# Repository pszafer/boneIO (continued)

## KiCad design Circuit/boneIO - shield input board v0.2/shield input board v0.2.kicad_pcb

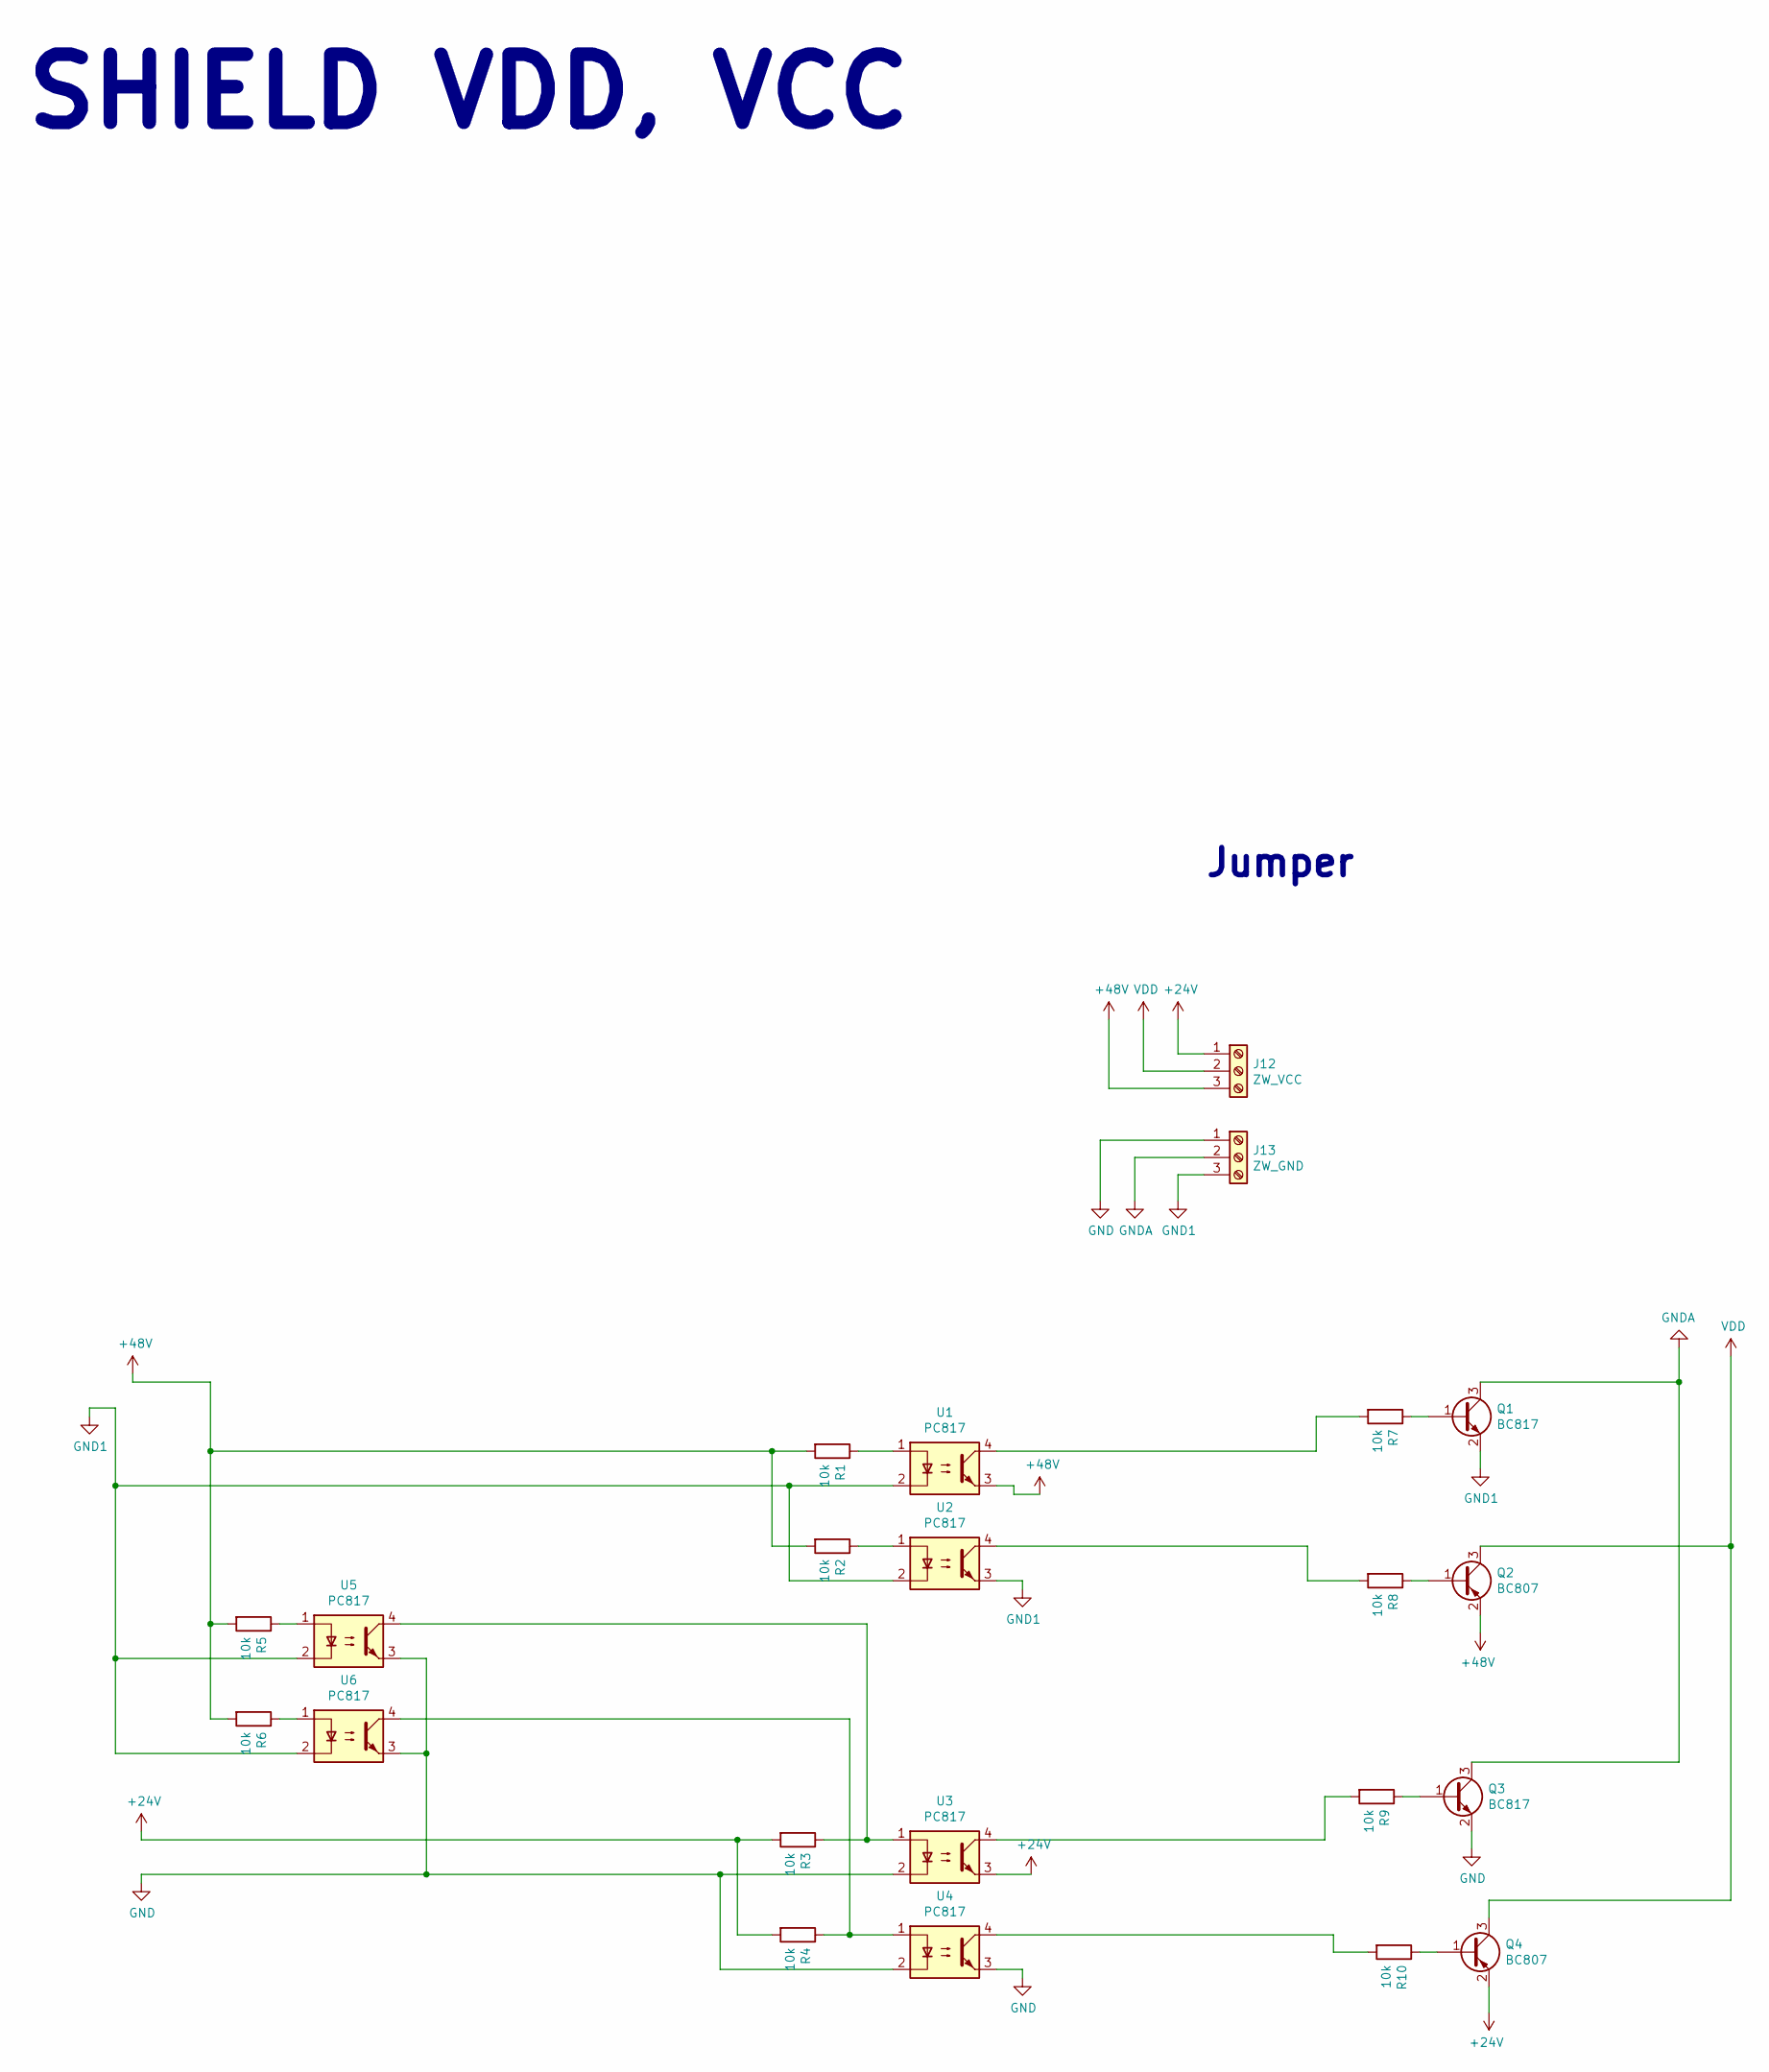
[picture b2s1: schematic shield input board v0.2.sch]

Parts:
J12: ZW_VCC; PinHeader_1x03_P2.54mm_Vertical
J13: ZW_GND; PinHeader_1x03_P2.54mm_Vertical
Q1, Q3: BC817; SOT-23
Q2, Q4: BC807; SOT-23
R1, R2, R3, R4, R5, R6, R7, R8, R9, R10: 10k; R_0603_1608Metric; JLCPCB C237118
U1, U2, U3, U4, U5, U6: PC817; DIP-4_W7.62mm; JLCPCB C6649

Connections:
+24V: J12.1, Q4.2 (E), R3.2, R4.2, U3.3
+48V: J12.3, Q2.2 (E), R1.2, R2.2, R5.2, R6.2, U1.3
GND: J13.1, Q3.2 (E), U3.2, U4.2, U4.3, U5.3, U6.3
GND1: J13.3, Q1.2 (E), U1.2, U2.2, U2.3, U5.2, U6.2
GNDA: J13.2, Q1.3 (C), Q3.3 (C)
unnamed: Q1.1 (B), R7.1
unnamed: Q2.1 (B), R8.1
unnamed: Q3.1 (B), R9.1
unnamed: Q4.1 (B), R10.1
unnamed: R1.1, U1.1
unnamed: R2.1, U2.1
unnamed: R3.1, U3.1, U5.4
unnamed: R4.1, U4.1, U6.4
unnamed: R5.1, U5.1
unnamed: R6.1, U6.1
unnamed: R7.2, U1.4
unnamed: R8.2, U2.4
unnamed: R9.2, U3.4
unnamed: R10.2, U4.4
VDD: J12.2, Q2.3 (C), Q4.3 (C)

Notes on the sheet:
Jumper
SHIELD VDD, VCC

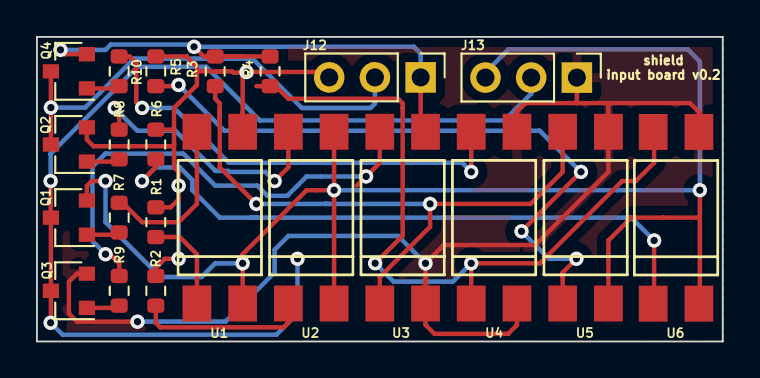
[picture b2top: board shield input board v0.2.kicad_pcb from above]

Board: 2 copper layers, 38.1 x 16.9 mm, 22 parts (0 on the bottom side), 20 nets.

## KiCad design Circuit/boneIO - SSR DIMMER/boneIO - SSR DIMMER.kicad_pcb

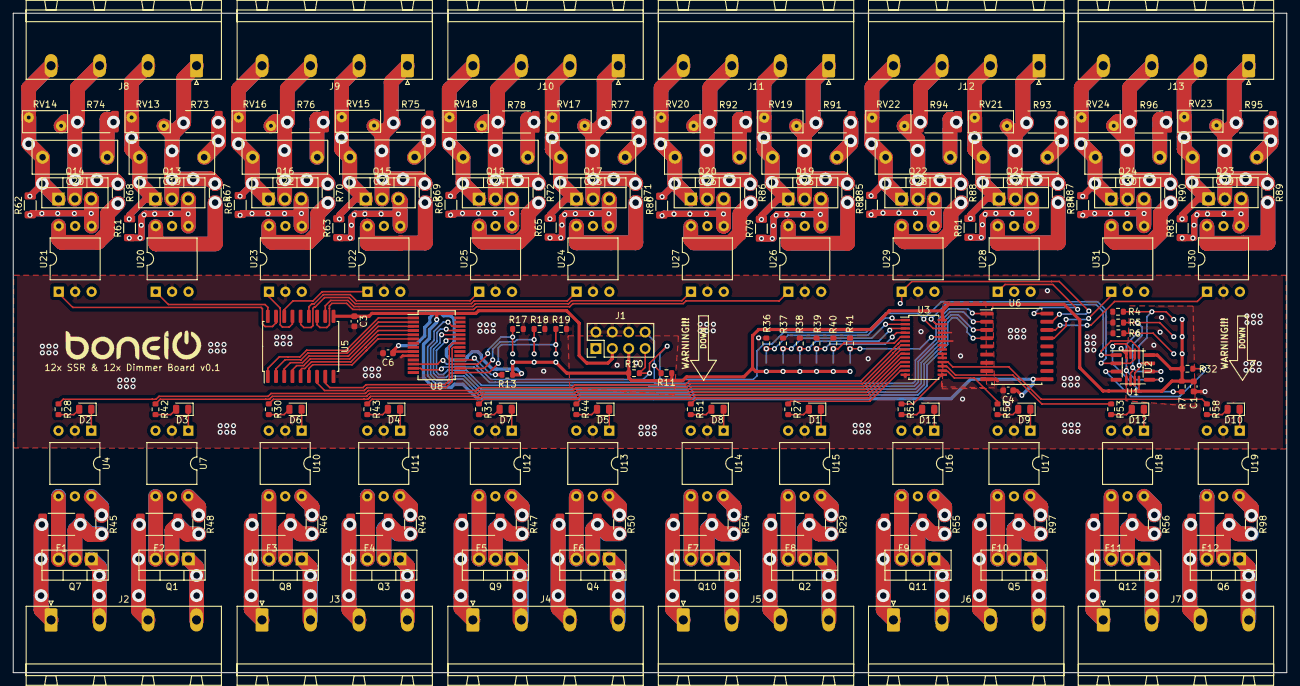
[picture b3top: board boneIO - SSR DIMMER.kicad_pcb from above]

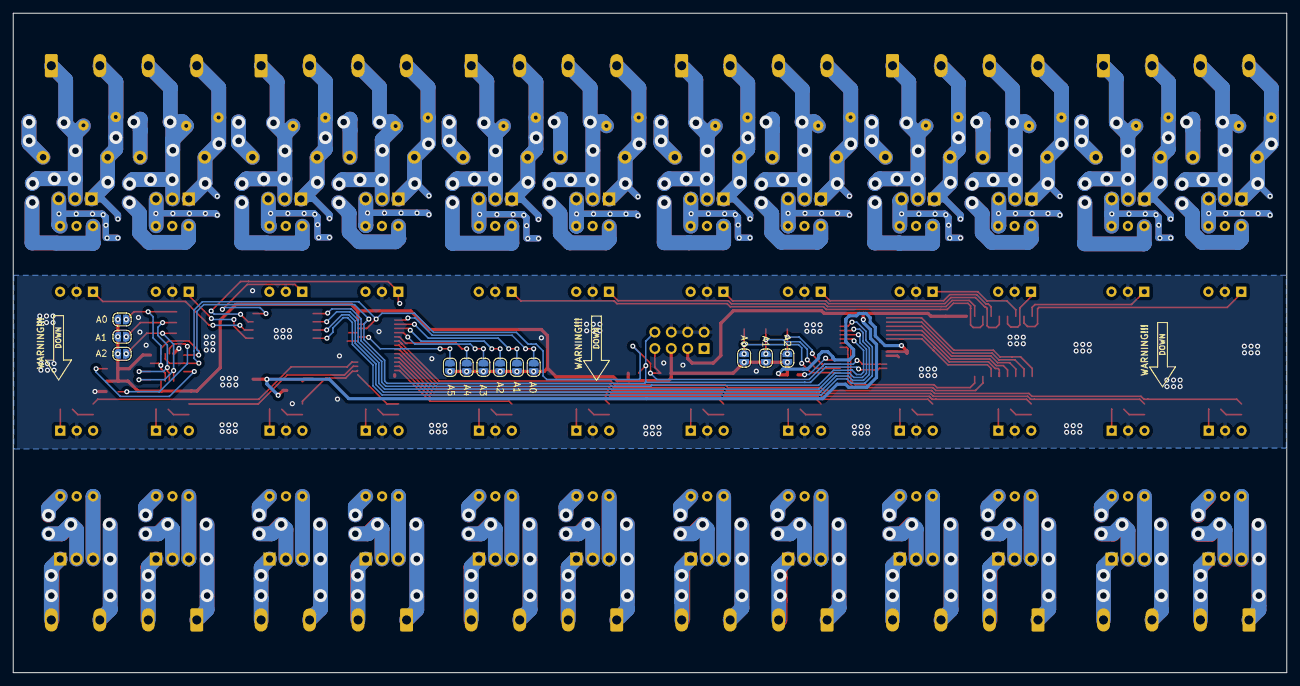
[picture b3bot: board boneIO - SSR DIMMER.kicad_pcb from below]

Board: 2 copper layers, 197.0 x 102.0 mm, 208 parts (12 on the bottom side), 200 nets.

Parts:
A0, A0#2, A0#3, A1, A1#2, A1#3, A2, A2#2, A2#3, A3, A4, A5: Jumper_NO_Small; SolderJumper-2_P1.3mm_Open_RoundedPad1.0x1.5mm
C1, C3, C4, C6: 100n; C_0603_1608Metric
C19, C20, C21, C22, C23, C24, C25, C26, C27, C28, C29, C30: MKP-X2-10NR10/275V; C_Rect_L13.0mm_W5.0mm_P10.00mm_FKS3_FKP3_MKS4
D1, D2, D3, D4, D5, D6, D7, D8, D9, D10, D11, D12: LED_ALT; LED_0805_2012Metric
F1, F2, F3, F4, F5, F6, F7, F8, F9, F10, F11, F12: 4A; Fuse_2512_6332Metric
J1: Conn_02x04_Odd_Even; PinHeader_2x04_P2.54mm_Vertical
J2, J3, J4, J5, J6, J7: DIMMER; PhoenixContact_GMSTBA_2,5_4-G_1x04_P7.50mm_Horizontal
J8, J9, J10, J11, J12, J13: Screw_Terminal_01x04; PhoenixContact_GMSTBA_2,5_4-G_1x04_P7.50mm_Horizontal
Q1, Q2, Q3, Q4, Q5, Q6, Q7, Q8, Q9, Q10, Q11, Q12: BT136-600; TO-220-3_Vertical
Q13, Q14, Q15, Q16, Q17, Q18, Q19, Q20, Q21, Q22, Q23, Q24: BTA12-600B; TO-220-3_Vertical
R4, R5, R6, R17, R18, R19, R36, R37, R38, R39, R40, R41: 10k; R_0603_1608Metric
R7, R10, R11, R13, R32: 4.7k; R_0603_1608Metric
R27, R28, R30, R31, R42, R43, R44, R51, R52, R53, R57, R58: 220R; R_0603_1608Metric
R29, R45, R46, R47, R48, R49, R50, R54, R55, R56, R97, R98: 1k; R_1206_3216Metric
R61, R62, R63, R64, R65, R66, R79, R80, R81, R82, R83, R84: 330R; R_1206_3216Metric
R67, R68, R69, R70, R71, R72, R85, R86, R87, R88, R89, R90: 360R; R_1206_3216Metric
R73, R74, R75, R76, R77, R78, R91, R92, R93, R94, R95, R96: 39R/2W; R_2512_6332Metric
RV13, RV14, RV15, RV16, RV17, RV18, RV19, RV20, RV21, RV22, RV23, RV24: JVR07N431K; RV_Disc_D7mm_W3.4mm_P5mm
U1: MCP9808-E_SO8; SO-8_3.9x4.9mm_P1.27mm
U2: MCP9808-E_MS; MSOP-8_3x3mm_P0.65mm
U3: PCA9685PW; TSSOP-28_4.4x9.7mm_P0.65mm
U4, U7, U10, U11, U12, U13, U14, U15, U16, U17, U18, U19, U20, U21, U22, U23, U24, U25, U26, U27, U28, U29, U30, U31: MOC3041M; DIP-6_W10.16mm
U5, U6: ULN2803A; SOIC-18W_7.5x11.6mm_P1.27mm
U8: MCP23017_SS; SSOP-28_5.3x10.2mm_P0.65mm

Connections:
+3V3: A0.1, A0#2.2, A0#3.1, A1.1, A1#2.2, A1#3.1, A2.1, A2#2.2, A2#3.1, A3.1, A4.1, A5.1, C1.1, C6.1, J1.5, R7.1, R10.1, R11.1, R13.1, R32.1, U1.8, U2.8, U3.28, U8.9
+5V: C3.1, C4.1, J1.3, U5.10, U6.10
GND: C1.2, C3.2, C4.2, C6.2, J1.2, J1.4, J1.6, R4.2, R5.2, R6.2, R17.2, R18.2, R19.2, R36.2, R37.2, R38.2, R39.2, R40.2, R41.2, U1.4, U2.4, U3.14, U3.23, U3.25, U4.2, U5.9, U6.9, U7.2, U8.10, U10.2, U11.2, U12.2, U13.2, U14.2, U15.2, U16.2, U17.2, U18.2, U19.2, U20.2, U21.2, U22.2, U23.2, U24.2, U25.2, U26.2, U27.2, U28.2, U29.2, U30.2, U31.2
K1: U5.1, U8.1
K2: U5.2, U8.2
K3: U5.3, U8.3
K4: U5.4, U8.4
K5: U5.5, U8.5
K6: U5.6, U8.6
K7: U5.7, U8.21
K8: U5.8, U8.22
K9: U6.1, U8.23
K10: U6.2, U8.24
K11: U6.3, U8.25
K12: U6.4, U8.26
unnamed: C19.1, R73.2
unnamed: C19.2, J8.2, Q13.1, R61.2, RV13.2
unnamed: C20.1, R74.2
unnamed: C20.2, J8.4, Q14.1, R62.2, RV14.2
unnamed: C21.1, R75.2
unnamed: C21.2, J9.2, Q15.1, R63.2, RV15.2
unnamed: C22.1, R76.2
unnamed: C22.2, J9.4, Q16.1, R64.2, RV16.2
unnamed: C23.1, R77.2
unnamed: C23.2, J10.2, Q17.1, R65.2, RV17.2
unnamed: C24.1, R78.2
unnamed: C24.2, J10.4, Q18.1, R66.2, RV18.2
unnamed: C25.1, R91.2
unnamed: C25.2, J11.2, Q19.1, R79.2, RV19.2
unnamed: C26.1, R92.2
unnamed: C26.2, J11.4, Q20.1, R80.2, RV20.2
unnamed: C27.1, R93.2
unnamed: C27.2, J12.2, Q21.1, R81.2, RV21.2
unnamed: C28.1, R94.2
unnamed: C28.2, J12.4, Q22.1, R82.2, RV22.2
unnamed: C29.1, R95.2
unnamed: C29.2, J13.2, Q23.1, R83.2, RV23.2
unnamed: C30.1, R96.2
unnamed: C30.2, J13.4, Q24.1, R84.2, RV24.2
unnamed: D1.1, U15.1
unnamed: D1.2, R27.2
unnamed: D2.1, U4.1
unnamed: D2.2, R28.2
unnamed: D3.1, U7.1
unnamed: D3.2, R42.2
unnamed: D4.1, U11.1
unnamed: D4.2, R43.2
unnamed: D5.1, U13.1
unnamed: D5.2, R44.2
unnamed: D6.1, U10.1
unnamed: D6.2, R30.2
unnamed: D7.1, U12.1
unnamed: D7.2, R31.2
unnamed: D8.1, U14.1
unnamed: D8.2, R51.2
unnamed: D9.1, U17.1
unnamed: D9.2, R57.2
unnamed: D10.1, U19.1
unnamed: D10.2, R58.2
unnamed: D11.1, U16.1
unnamed: D11.2, R52.2
unnamed: D12.1, U18.1
unnamed: D12.2, R53.2
unnamed: F1.1, Q7.2, R45.2
unnamed: F1.2, J2.1
unnamed: F2.1, Q1.2, R48.2
unnamed: F2.2, J2.3
unnamed: F3.1, Q8.2, R46.2
unnamed: F3.2, J3.1
unnamed: F4.1, Q3.2, R49.2
unnamed: F4.2, J3.3
unnamed: F5.1, Q9.2, R47.2
unnamed: F5.2, J4.1
unnamed: F6.1, Q4.2, R50.2
unnamed: F6.2, J4.3
unnamed: F7.1, Q10.2, R54.2
unnamed: F7.2, J5.1
unnamed: F8.1, Q2.2, R29.2
unnamed: F8.2, J5.3
unnamed: F9.1, Q11.2, R55.2
unnamed: F9.2, J6.1
unnamed: F10.1, Q5.2, R97.2
unnamed: F10.2, J6.3
unnamed: F11.1, Q12.2, R56.2
unnamed: F11.2, J7.1
unnamed: F12.1, Q6.2, R98.2
unnamed: F12.2, J7.3
unnamed: J2.2, Q7.1
unnamed: J2.4, Q1.1
unnamed: J3.2, Q8.1
unnamed: J3.4, Q3.1
unnamed: J4.2, Q9.1
unnamed: J4.4, Q4.1
unnamed: J5.2, Q10.1
unnamed: J5.4, Q2.1
unnamed: J6.2, Q11.1
unnamed: J6.4, Q5.1
unnamed: J7.2, Q12.1
unnamed: J7.4, Q6.1
unnamed: J8.1, Q13.2, R67.1, R73.1, RV13.1
unnamed: J8.3, Q14.2, R68.1, R74.1, RV14.1
unnamed: J9.1, Q15.2, R69.1, R75.1, RV15.1
unnamed: J9.3, Q16.2, R70.1, R76.1, RV16.1
unnamed: J10.1, Q17.2, R71.1, R77.1, RV17.1
unnamed: J10.3, Q18.2, R72.1, R78.1, RV18.1
unnamed: J11.1, Q19.2, R85.1, R91.1, RV19.1
unnamed: J11.3, Q20.2, R86.1, R92.1, RV20.1
unnamed: J12.1, Q21.2, R87.1, R93.1, RV21.1
unnamed: J12.3, Q22.2, R88.1, R94.1, RV22.1
unnamed: J13.1, Q23.2, R89.1, R95.1, RV23.1
unnamed: J13.3, Q24.2, R90.1, R96.1, RV24.1
unnamed: A0#3.2, R4.1, U1.7, U2.7
unnamed: A1#3.2, R5.1, U1.6, U2.6
unnamed: A2#3.2, R6.1, U1.5, U2.5
unnamed: A2#2.1, R17.1, U8.17
unnamed: A1#2.1, R18.1, U8.16
unnamed: A0#2.1, R19.1, U8.15
unnamed: A0.2, R36.1, U3.1
unnamed: A1.2, R37.1, U3.2
unnamed: A2.2, R38.1, U3.3
unnamed: A3.2, R39.1, U3.4
unnamed: A4.2, R40.1, U3.5
unnamed: A5.2, R41.1, U3.24
unnamed: Q1.3, U7.4
unnamed: Q2.3, U15.4
unnamed: Q3.3, U11.4
unnamed: Q4.3, U13.4
unnamed: Q5.3, U17.4
unnamed: Q6.3, U19.4
unnamed: Q7.3, U4.4
unnamed: Q8.3, U10.4
unnamed: Q9.3, U12.4
unnamed: Q10.3, U14.4
unnamed: Q11.3, U16.4
unnamed: Q12.3, U18.4
unnamed: Q13.3, R61.1, U20.4
unnamed: Q14.3, R62.1, U21.4
unnamed: Q15.3, R63.1, U22.4
unnamed: Q16.3, R64.1, U23.4
unnamed: Q17.3, R65.1, U24.4
unnamed: Q18.3, R66.1, U25.4
unnamed: Q19.3, R79.1, U26.4
unnamed: Q20.3, R80.1, U27.4
unnamed: Q21.3, R81.1, U28.4
unnamed: Q22.3, R82.1, U29.4
unnamed: Q23.3, R83.1, U30.4
unnamed: Q24.3, R84.1, U31.4
unnamed: R7.2, U2.3
unnamed: R13.2, U8.18
unnamed: R29.1, U15.6
unnamed: R32.2, U1.3
unnamed: R45.1, U4.6
unnamed: R46.1, U10.6
unnamed: R47.1, U12.6
unnamed: R48.1, U7.6
unnamed: R49.1, U11.6
unnamed: R50.1, U13.6
unnamed: R54.1, U14.6
unnamed: R55.1, U16.6
unnamed: R56.1, U18.6
unnamed: R67.2, U20.6
unnamed: R68.2, U21.6
unnamed: R69.2, U22.6
unnamed: R70.2, U23.6
unnamed: R71.2, U24.6
unnamed: R72.2, U25.6
unnamed: R85.2, U26.6
unnamed: R86.2, U27.6
unnamed: R87.2, U28.6
unnamed: R88.2, U29.6
unnamed: R89.2, U30.6
unnamed: R90.2, U31.6
unnamed: R97.1, U17.6
unnamed: R98.1, U19.6
PWM1: R28.1, U3.6
PWM2: R42.1, U3.7
PWM3: R30.1, U3.8
PWM4: R43.1, U3.9
PWM5: R31.1, U3.10
PWM6: R44.1, U3.11
PWM7: R51.1, U3.12
PWM8: R27.1, U3.13
PWM9: R52.1, U3.15
PWM10: R57.1, U3.16
PWM11: R53.1, U3.17
PWM12: R58.1, U3.18
RELAY1: U5.18, U20.1
RELAY2: U5.17, U21.1
RELAY3: U5.16, U22.1
RELAY4: U5.15, U23.1
RELAY5: U5.14, U24.1
RELAY6: U5.13, U25.1
RELAY7: U5.12, U26.1
RELAY8: U5.11, U27.1
RELAY9: U6.18, U28.1
RELAY10: U6.17, U29.1
RELAY11: U6.16, U30.1
RELAY12: U6.15, U31.1
SCL: J1.7, R10.2, U1.2, U2.2, U3.26, U8.12
SDA: J1.8, R11.2, U1.1, U2.1, U3.27, U8.13

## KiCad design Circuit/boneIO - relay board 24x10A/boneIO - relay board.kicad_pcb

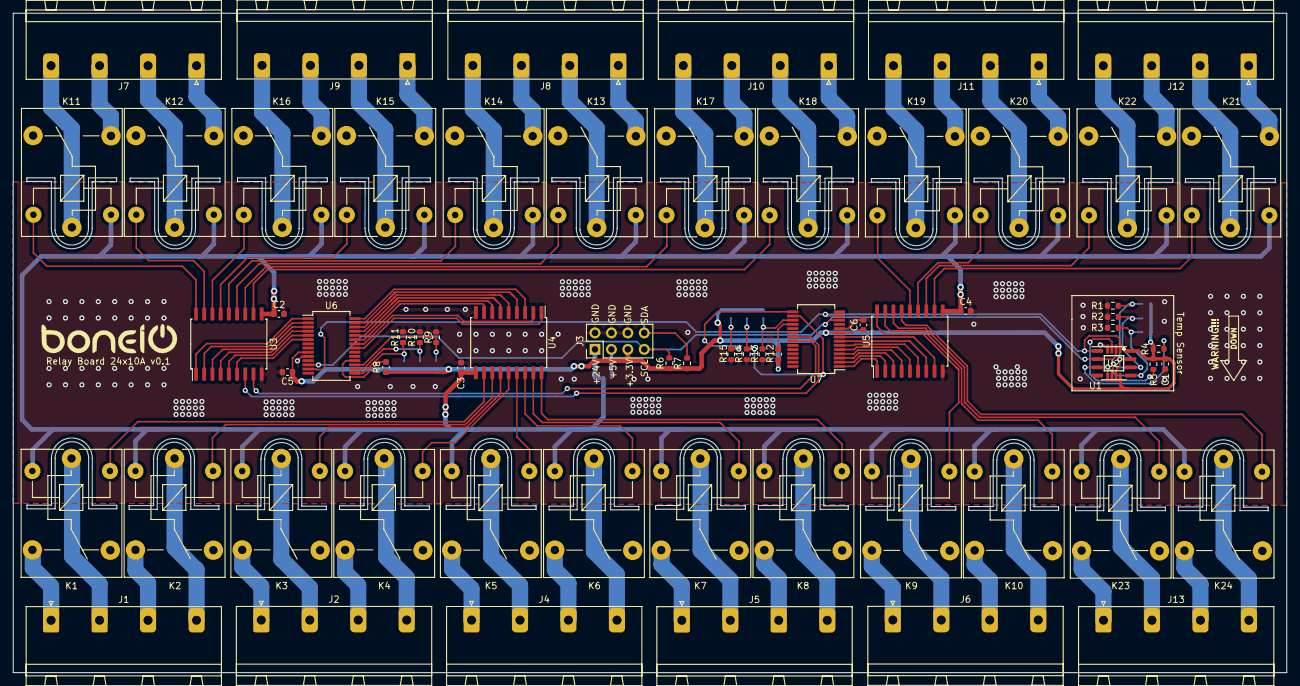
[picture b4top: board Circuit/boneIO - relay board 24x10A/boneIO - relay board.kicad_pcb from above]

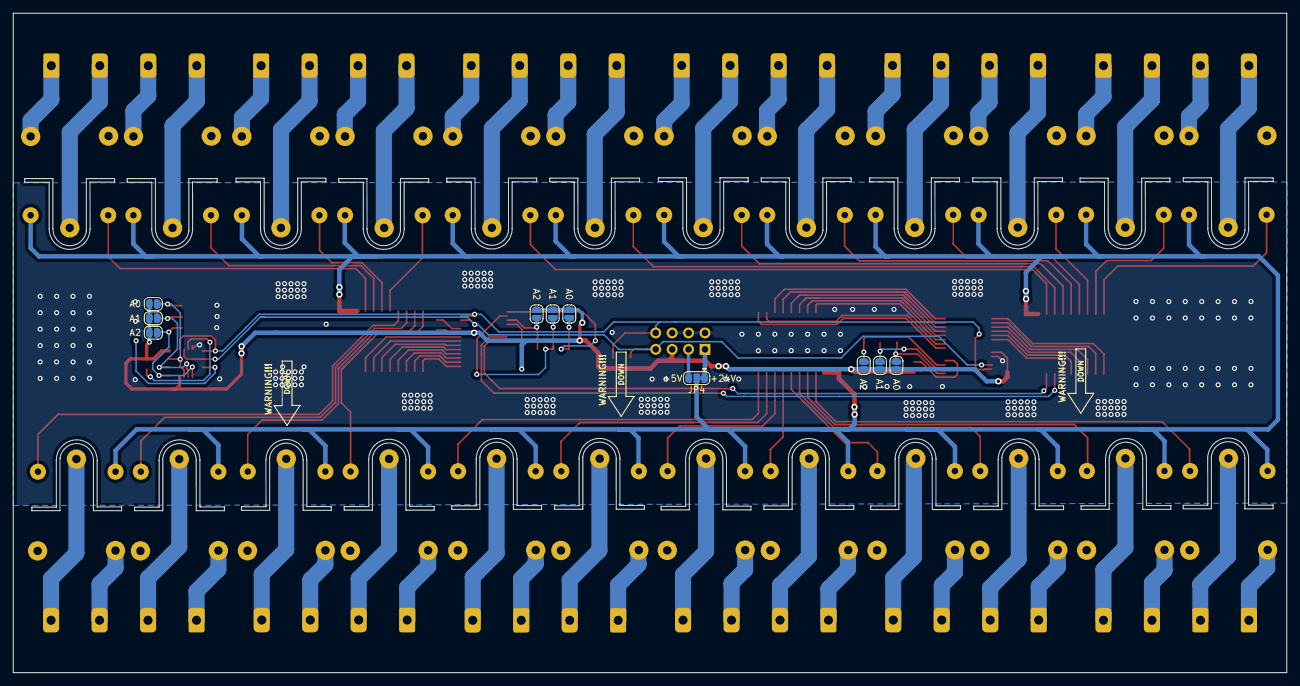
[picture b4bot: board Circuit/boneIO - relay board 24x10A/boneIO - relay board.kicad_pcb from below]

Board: 2 copper layers, 197.0 x 102.0 mm, 75 parts (10 on the bottom side), 116 nets.

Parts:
A0, A0#2, A0#3, A1, A1#2, A1#3, A2, A2#2, A2#3: NO_Small; SolderJumper-2_P1.3mm_Open_RoundedPad1.0x1.5mm
C1, C2, C3, C4, C5, C6: 100n; C_0603_1608Metric
J1, J2, J4, J5, J6, J7, J8, J9, J10, J11, J12, J13: Screw_Terminal_01x04; PhoenixContact_GMSTBA_2,5_4-G_1x04_P7.50mm_Horizontal
J3: Conn_02x04_Odd_Even; PinHeader_2x04_P2.54mm_Vertical
JP4: SolderJumper_3_Bridged12; SolderJumper-3_P1.3mm_Bridged12_RoundedPad1.0x1.5mm
K1, K2, K3, K4, K5, K6, K7, K8, K9, K10, K11, K12, K13, K14, K15, K16, K17, K18, K19, K20, K21, K22, K23, K24: SANYOU_SRD_Form_C; Relay_SPDT_SANYOU_SRD_Series_Form_C
R1, R2, R3, R9, R10, R11, R13, R14, R15: 10k; R_0603_1608Metric
R4, R5, R6, R7, R8, R12: 4.7k; R_0603_1608Metric
U1: MCP9808-E_SO8; SO-8_3.9x4.9mm_P1.27mm
U2: MCP9808-E_MS; SOP65P490X110-8N
U3, U4, U5: ULN2803A; SOIC-18W_7.5x11.6mm_P1.27mm
U6, U7: MCP23017_SS; SSOP-28_5.3x10.2mm_P0.65mm

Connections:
+3V3: A0.1, A0#2.1, A0#3.1, A1.1, A1#2.1, A1#3.1, A2.1, A2#2.1, A2#3.1, C1.1, C5.1, C6.1, J3.5, R4.1, R5.1, R6.1, R7.1, R8.1, R12.1, U1.8, U2.8, U6.9, U7.9
+5V: J3.3, JP4.3
+24V: J3.1, JP4.1
GND: C1.2, C2.2, C3.2, C4.2, C5.2, C6.2, J3.2, J3.4, J3.6, R1.2, R2.2, R3.2, R9.2, R10.2, R11.2, R13.2, R14.2, R15.2, U1.4, U2.4, U3.9, U4.9, U5.9, U6.10, U7.10
K1: U3.1, U6.1
K2: U3.2, U6.2
K3: U3.3, U6.3
K4: U3.4, U6.4
K5: U3.5, U6.5
K6: U3.6, U6.6
K7: U5.4, U7.4
K8: U5.3, U7.3
K9: U5.2, U7.2
K10: U5.1, U7.1
K11: U4.8, U6.23
K12: U4.7, U6.24
K13: U4.6, U6.25
K14: U4.5, U6.26
K15: U4.4, U6.27
K16: U4.3, U6.28
K17: U5.8, U7.8
K18: U5.7, U7.7
K19: U5.6, U7.6
K20: U5.5, U7.5
K21: U3.7, U7.21
K22: U3.8, U7.22
K23: U4.1, U6.21
K24: U4.2, U6.22
unnamed: J1.1, K1.3
unnamed: J1.2, K1.1
unnamed: J1.3, K2.3
unnamed: J1.4, K2.1
unnamed: J2.1, K3.3
unnamed: J2.2, K3.1
unnamed: J2.3, K4.3
unnamed: J2.4, K4.1
unnamed: J4.1, K5.3
unnamed: J4.2, K5.1
unnamed: J4.3, K6.3
unnamed: J4.4, K6.1
unnamed: J5.1, K7.3
unnamed: J5.2, K7.1
unnamed: J5.3, K8.3
unnamed: J5.4, K8.1
unnamed: J6.1, K9.3
unnamed: J6.2, K9.1
unnamed: J6.3, K10.3
unnamed: J6.4, K10.1
unnamed: J7.1, K12.3
unnamed: J7.2, K12.1
unnamed: J7.3, K11.3
unnamed: J7.4, K11.1
unnamed: J8.1, K13.3
unnamed: J8.2, K13.1
unnamed: J8.3, K14.3
unnamed: J8.4, K14.1
unnamed: J9.1, K15.3
unnamed: J9.2, K15.1
unnamed: J9.3, K16.3
unnamed: J9.4, K16.1
unnamed: J10.1, K18.3
unnamed: J10.2, K18.1
unnamed: J10.3, K17.3
unnamed: J10.4, K17.1
unnamed: J11.1, K20.3
unnamed: J11.2, K20.1
unnamed: J11.3, K19.3
unnamed: J11.4, K19.1
unnamed: J12.1, K21.3
unnamed: J12.2, K21.1
unnamed: J12.3, K22.3
unnamed: J12.4, K22.1
unnamed: J13.1, K23.3
unnamed: J13.2, K23.1
unnamed: J13.3, K24.3
unnamed: J13.4, K24.1
unnamed: A0#3.2, R1.1, U1.7, U2.7
unnamed: A1#3.2, R2.1, U1.6, U2.6
unnamed: A2#3.2, R3.1, U1.5, U2.5
unnamed: A2#2.2, R9.1, U6.17
unnamed: A1#2.2, R10.1, U6.16
unnamed: A0#2.2, R11.1, U6.15
unnamed: A2.2, R13.1, U7.17
unnamed: A1.2, R14.1, U7.16
unnamed: A0.2, R15.1, U7.15
unnamed: R4.2, U1.3
unnamed: R5.2, U2.3
unnamed: R8.2, U6.18
unnamed: R12.2, U7.18
RELAY1: K1.5, U4.11
RELAY2: K2.5, U4.12
RELAY3: K3.5, U4.13
RELAY4: K4.5, U4.14
RELAY5: K5.5, U4.15
RELAY6: K6.5, U4.16
RELAY7: K7.5, U4.17
RELAY8: K8.5, U4.18
RELAY9: K9.5, U5.18
RELAY10: K10.5, U5.17
RELAY11: K11.5, U3.18
RELAY12: K12.5, U3.17
RELAY13: K16.5, U3.16
RELAY14: K15.5, U3.15
RELAY15: K14.5, U3.14
RELAY16: K13.5, U3.13
RELAY17: K17.5, U3.12
RELAY18: K18.5, U3.11
RELAY19: K19.5, U5.14
RELAY20: K20.5, U5.13
RELAY21: K21.5, U5.11
RELAY22: K22.5, U5.12
RELAY23: K23.5, U5.16
RELAY24: K24.5, U5.15
SCL: J3.7, R6.2, U1.2, U2.2, U6.12, U7.12
SDA: J3.8, R7.2, U1.1, U2.1, U6.13, U7.13
VCC: C2.1, C3.1, C4.1, JP4.2, K1.2, K2.2, K3.2, K4.2, K5.2, K6.2, K7.2, K8.2, K9.2, K10.2, K11.2, K12.2, K13.2, K14.2, K15.2, K16.2, K17.2, K18.2, K19.2, K20.2, K21.2, K22.2, K23.2, K24.2, U3.10, U4.10, U5.10

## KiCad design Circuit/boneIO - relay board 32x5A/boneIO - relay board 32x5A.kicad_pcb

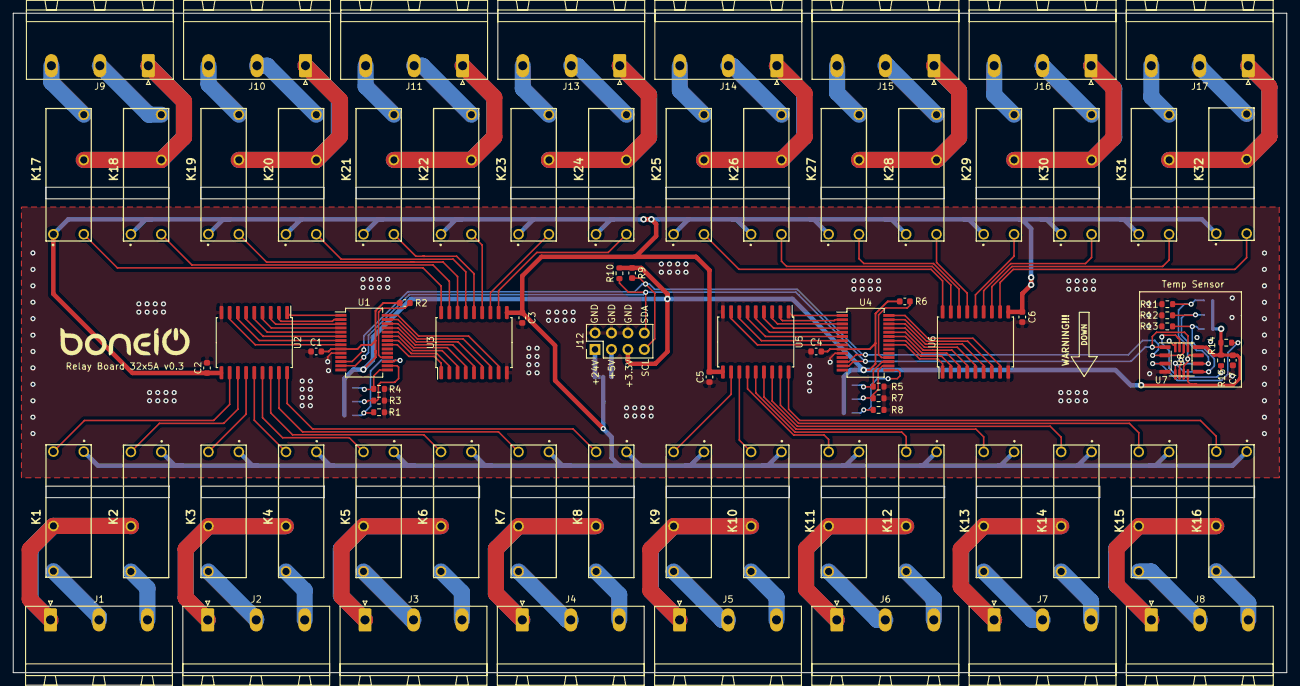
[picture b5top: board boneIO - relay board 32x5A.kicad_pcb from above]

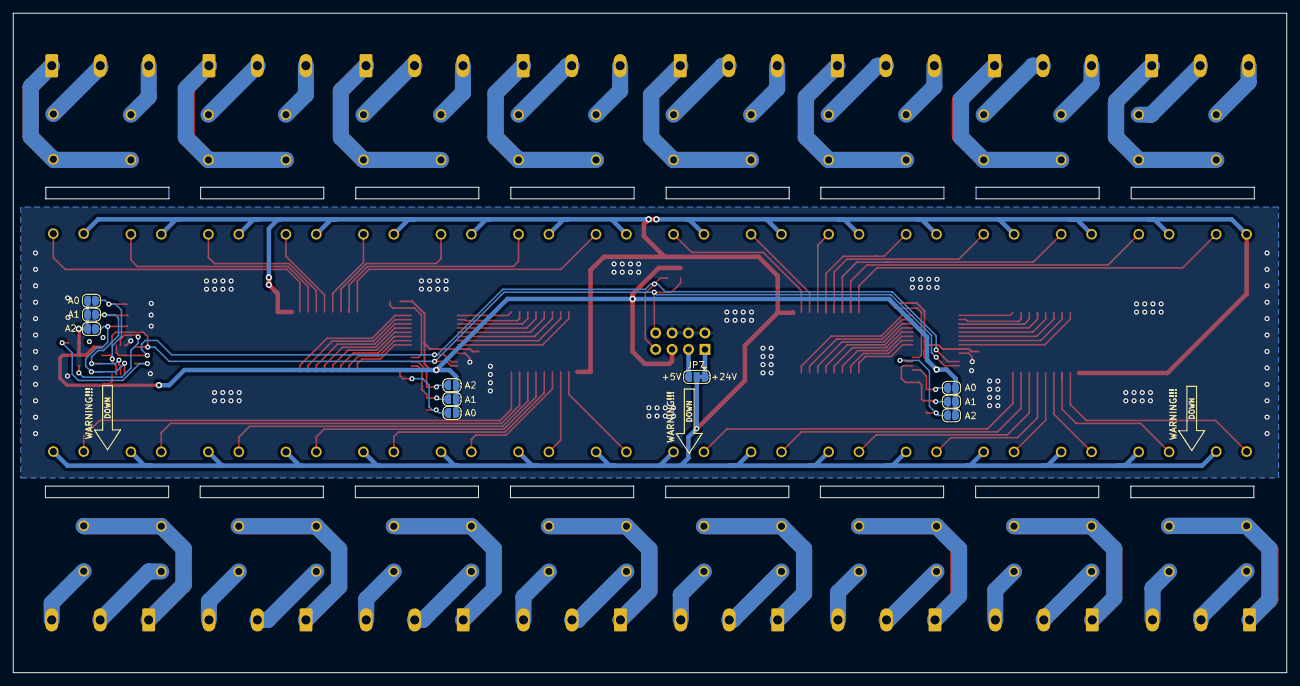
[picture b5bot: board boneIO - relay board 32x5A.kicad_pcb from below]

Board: 2 copper layers, 197.0 x 102.0 mm, 89 parts (10 on the bottom side), 132 nets.

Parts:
A0, A0#2, A0#3, A1, A1#2, A1#3, A2, A2#2, A2#3: NO_Small; SolderJumper-2_P1.3mm_Open_RoundedPad1.0x1.5mm
C1, C2, C3, C4, C5, C6: 100nF; C_0603_1608Metric
C7: 100n; C_0603_1608Metric
J1, J2, J3, J4, J5, J6, J7, J8, J9, J10, J11, J13, J14, J15, J16, J17: Screw_Terminal_01x03; PhoenixContact_GMSTBA_2,5_3-G_1x03_P7.50mm_Horizontal
J12: Conn_02x04_Odd_Even; PinHeader_2x04_P2.54mm_Vertical
JP7: SolderJumper_3_Open; SolderJumper-3_P1.3mm_Bridged12_RoundedPad1.0x1.5mm
K1, K2, K3, K4, K5, K6, K7, K8, K9, K10, K11, K12, K13, K14, K15, K16, K17, K18, K19, K20, K21, K22, K23, K24, K25, K26, K27, K28, K29, K30, K31, K32: HF46F
R1, R3, R4, R5, R7, R8, R11, R12, R13: 10k; R_0603_1608Metric
R2, R6, R9, R10, R14, R15: 4.7k; R_0603_1608Metric
U1, U4: MCP23017_SS; SSOP-28_5.3x10.2mm_P0.65mm
U2, U3, U5, U6: ULN2803A; SOIC-18W_7.5x11.6mm_P1.27mm
U7: MCP9808_SO8; SO-8_3.9x4.9mm_P1.27mm
U8: MCP9808_MSOP; MSOP-8_3x3mm_P0.65mm

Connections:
+3V3: A0.1, A0#2.1, A0#3.1, A1.1, A1#2.1, A1#3.1, A2.1, A2#2.1, A2#3.1, C1.2, C4.2, C7.1, J12.5, R2.2, R6.2, R9.2, R10.2, R14.1, R15.1, U1.9, U4.9, U7.8, U8.8
+5V: J12.3, JP7.3
+24V: J12.1, JP7.1
GND: C1.1, C2.1, C3.1, C4.1, C5.1, C6.1, C7.2, J12.2, J12.4, J12.6, R1.2, R3.2, R4.2, R5.2, R7.2, R8.2, R11.2, R12.2, R13.2, U1.10, U2.9, U3.9, U4.10, U5.9, U6.9, U7.4, U8.4
unnamed: J1.1, K1.3, K2.3
unnamed: J1.2, K1.4
unnamed: J1.3, K2.4
unnamed: J2.1, K3.3, K4.3
unnamed: J2.2, K3.4
unnamed: J2.3, K4.4
unnamed: J3.1, K5.3, K6.3
unnamed: J3.2, K5.4
unnamed: J3.3, K6.4
unnamed: J4.1, K7.3, K8.3
unnamed: J4.2, K7.4
unnamed: J4.3, K8.4
unnamed: J5.1, K9.3, K10.3
unnamed: J5.2, K9.4
unnamed: J5.3, K10.4
unnamed: J6.1, K11.3, K12.3
unnamed: J6.2, K11.4
unnamed: J6.3, K12.4
unnamed: J7.1, K13.3, K14.3
unnamed: J7.2, K13.4
unnamed: J7.3, K14.4
unnamed: J8.1, K15.3, K16.3
unnamed: J8.2, K15.4
unnamed: J8.3, K16.4
unnamed: J9.1, K17.3, K18.3
unnamed: J9.2, K18.4
unnamed: J9.3, K17.4
unnamed: J10.1, K19.3, K20.3
unnamed: J10.2, K20.4
unnamed: J10.3, K19.4
unnamed: J11.1, K21.3, K22.3
unnamed: J11.2, K22.4
unnamed: J11.3, K21.4
unnamed: J13.1, K23.3, K24.3
unnamed: J13.2, K24.4
unnamed: J13.3, K23.4
unnamed: J14.1, K25.3, K26.3
unnamed: J14.2, K26.4
unnamed: J14.3, K25.4
unnamed: J15.1, K27.3, K28.3
unnamed: J15.2, K28.4
unnamed: J15.3, K27.4
unnamed: J16.1, K29.3, K30.3
unnamed: J16.2, K30.4
unnamed: J16.3, K29.4
unnamed: J17.1, K31.3, K32.3
unnamed: J17.2, K32.4
unnamed: J17.3, K31.4
unnamed: A2#3.2, R1.1, U1.17
unnamed: A1#3.2, R3.1, U1.16
unnamed: A0#3.2, R4.1, U1.15
unnamed: A2#2.2, R5.1, U4.17
unnamed: A1#2.2, R7.1, U4.16
unnamed: A0#2.2, R8.1, U4.15
unnamed: A0.2, R11.1, U7.7, U8.7
unnamed: A1.2, R12.1, U7.6, U8.6
unnamed: A2.2, R13.1, U7.5, U8.5
unnamed: R2.1, U1.18
unnamed: R6.1, U4.18
unnamed: R14.2, U7.3
unnamed: R15.2, U8.3
unnamed: U1.1, U2.1
unnamed: U1.2, U2.2
unnamed: U1.3, U2.3
unnamed: U1.4, U2.4
unnamed: U1.5, U2.5
unnamed: U1.6, U2.6
unnamed: U1.7, U2.7
unnamed: U1.8, U2.8
unnamed: U1.21, U3.1
unnamed: U1.22, U3.2
unnamed: U1.23, U3.3
unnamed: U1.24, U3.4
unnamed: U1.25, U3.5
unnamed: U1.26, U3.6
unnamed: U1.27, U3.7
unnamed: U1.28, U3.8
unnamed: U4.1, U5.1
unnamed: U4.2, U5.2
unnamed: U4.3, U5.3
unnamed: U4.4, U5.4
unnamed: U4.5, U5.5
unnamed: U4.6, U5.6
unnamed: U4.7, U5.7
unnamed: U4.8, U5.8
unnamed: U4.21, U6.1
unnamed: U4.22, U6.2
unnamed: U4.23, U6.3
unnamed: U4.24, U6.4
unnamed: U4.25, U6.5
unnamed: U4.26, U6.6
unnamed: U4.27, U6.7
unnamed: U4.28, U6.8
RELAY1: K1.2, U2.11
RELAY2: K2.2, U2.12
RELAY3: K3.2, U2.13
RELAY4: K4.2, U2.14
RELAY5: K5.2, U2.15
RELAY6: K6.2, U2.16
RELAY7: K7.2, U2.17
RELAY8: K8.2, U2.18
RELAY9: K9.2, U5.11
RELAY10: K10.2, U5.12
RELAY11: K11.2, U5.13
RELAY12: K12.2, U5.14
RELAY13: K13.2, U5.15
RELAY14: K14.2, U5.16
RELAY15: K15.2, U5.17
RELAY16: K16.2, U5.18
RELAY17: K17.2, U3.18
RELAY18: K18.2, U3.17
RELAY19: K19.2, U3.16
RELAY20: K20.2, U3.15
RELAY21: K21.2, U3.14
RELAY22: K22.2, U3.13
RELAY23: K23.2, U3.12
RELAY24: K24.2, U3.11
RELAY25: K25.2, U6.18
RELAY26: K26.2, U6.17
RELAY27: K27.2, U6.16
RELAY28: K28.2, U6.15
RELAY29: K29.2, U6.14
RELAY30: K30.2, U6.13
RELAY31: K31.2, U6.12
RELAY32: K32.2, U6.11
SCL: J12.7, R9.1, U1.12, U4.12, U7.2, U8.2
SDA: J12.8, R10.1, U1.13, U4.13, U7.1, U8.1
VCC: C2.2, C3.2, C5.2, C6.2, JP7.2, K1.1, K2.1, K3.1, K4.1, K5.1, K6.1, K7.1, K8.1, K9.1, K10.1, K11.1, K12.1, K13.1, K14.1, K15.1, K16.1, K17.1, K18.1, K19.1, K20.1, K21.1, K22.1, K23.1, K24.1, K25.1, K26.1, K27.1, K28.1, K29.1, K30.1, K31.1, K32.1, U2.10, U3.10, U5.10, U6.10
